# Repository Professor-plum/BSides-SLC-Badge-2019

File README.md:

# BSides-SLC-Badge-2019
source code, design files and artwork used in the BSides SLC 2019 badge

The following libraries were utilized in this project

https://github.com/rogerclarkmelbourne/Arduino_STM32
https://github.com/PaulStoffregen/SerialFlash
https://github.com/PaulStoffregen/XPT2046_Touchscreen

After installing these libraries, one edit needs to be made:

```
vim ~/Documents/Arduino/libraries/SerialFlash/SerialFlashChip.cpp
```

On line 161, change `SPIPORT.transfer(p, rdlen);` to be `SPIPORT.read(p, rdlen);`. I'm not sure if this is a bug in SerialFlash, or if SerialFlash was just designed to use a different STM32 library.

Now, in the Arduino IDE, you can open `src/BsidesSLCBig/BsidesSLCBig.ino`. Compile using the following board settings:

```
Board: "Generic STM32F103C Series"
Variant: "STM32F103CB (20k RAM, 128k Flash)"
```

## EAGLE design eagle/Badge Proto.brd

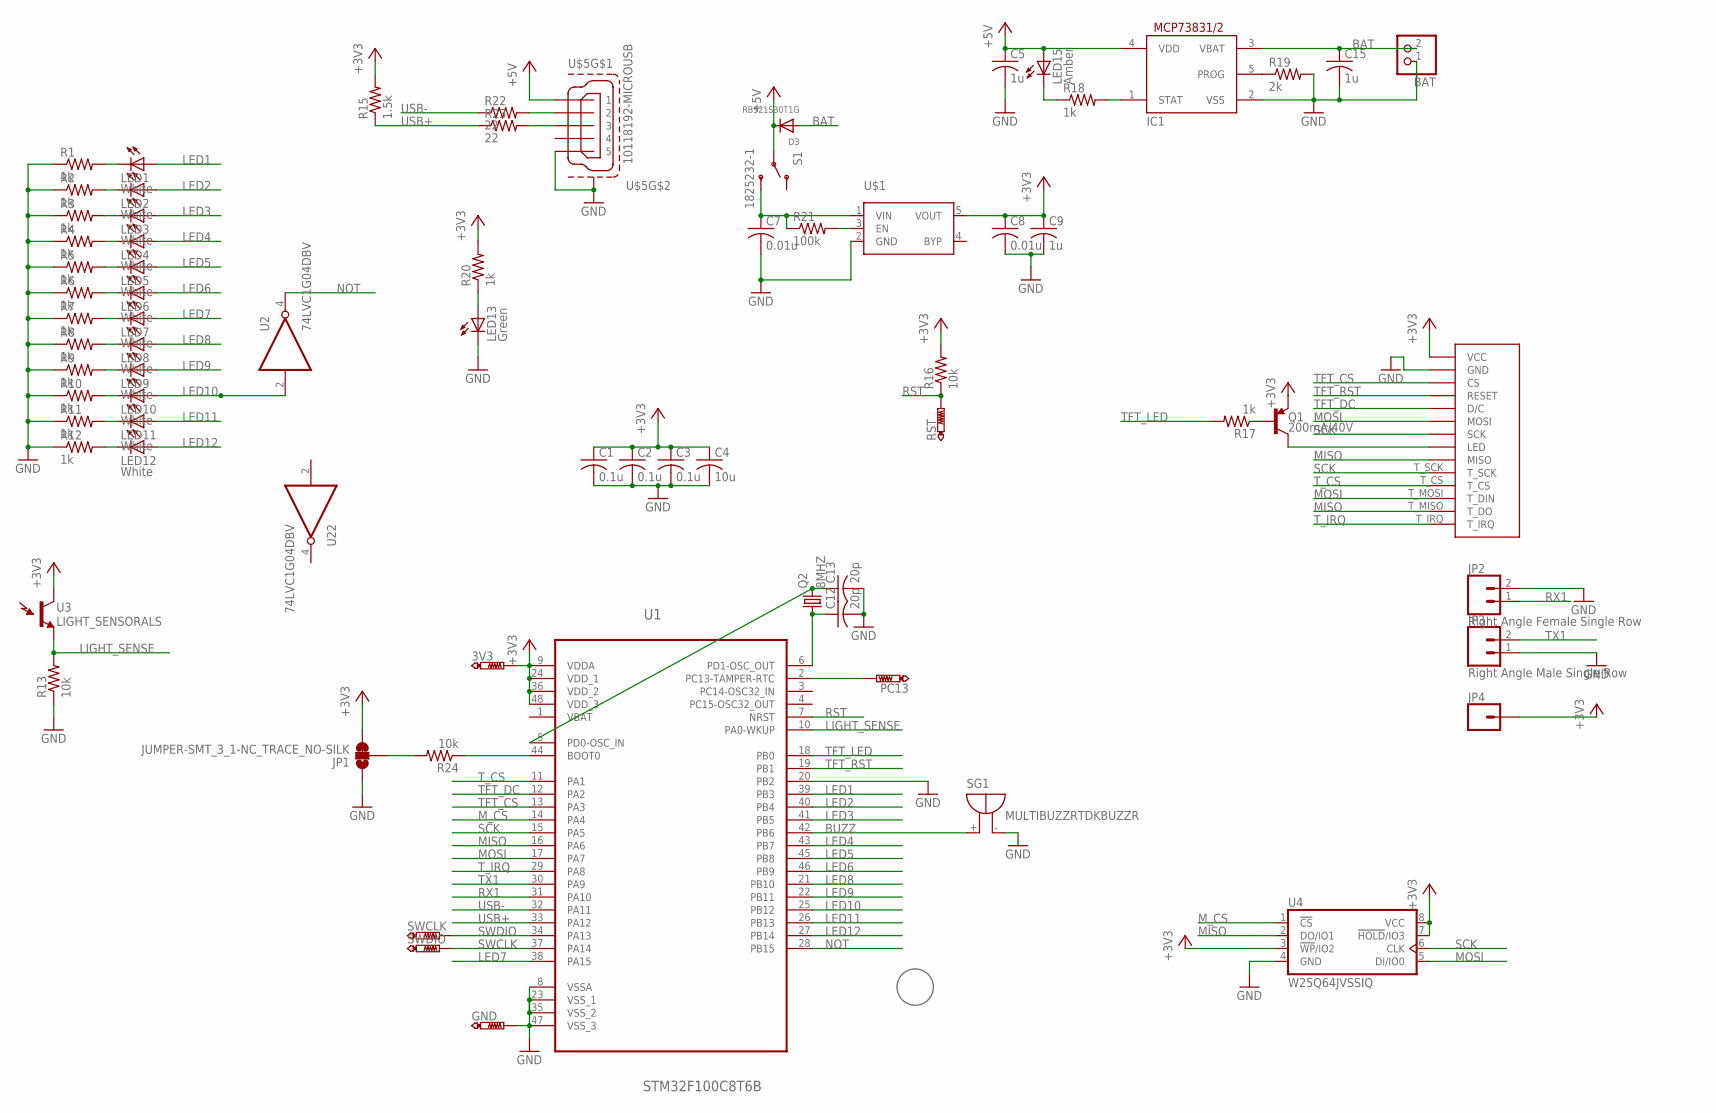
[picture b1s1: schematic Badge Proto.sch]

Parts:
3V3: PTR1TP15R; TP15R
BAT: JST_2PIN-THM-RA; JST-PH-2-THM-RA
C1, C2, C3: 0.1u; C0603K; MPN MC0603B104K160CT
C4: 10u; C0603K; MPN C1608X5R1A106K080AC
C5, C9, C15: 1u; C0603K; MPN C0603C104K8RACTU
C7, C8: 0.01u; C0603K
C12, C13: 20p; C0603K
D3: RB521S30T1G; SOD-523; MPN 1N4148WT.
GND: PTR1TP15R; TP15R
IC1: MCP73831/OT; SOT23-5L
J1: SPI_TFT_DISPLAY_TOUCH_NOSD; SPI_DISPLAY_TOUCH_NOSD
JP1: JUMPER-SMT_3_1-NC_TRACE_NO-SILK; SMT-JUMPER_3_1-NC_TRACE_NO-SILK
JP2: Right Angle Female Single Row; 1X02_RA_PTH_FEMALE
JP3: Right Angle Male Single Row; 1X02_RA_PTH_FEMALE
JP4: CONN_01PTH_NO_SILK_YES_STOP; 1X01_NO_SILK
LED1, LED2, LED3, LED4, LED5, LED6, LED7, LED8, LED9, LED10, LED11, LED12: White; SML0603
LED13: Green; SML0603
LED15: Amber; SML0603; MPN ASMT-RJ45-AQ502
PC13: PTR1TP15R; TP15R
Q1: 200mA/40V; SOT23-3
Q2: 8MHZ; HC49/S
R1, R2, R3, R4, R5, R6, R7, R8, R9, R10, R11, R12, R17, R18, R20: 1k; R0603; MPN ERJ-3GEYJ912V
R13, R16, R24: 10k; R0603; MPN RR0816P-103-D
R15: 1.5k; R0603; MPN MC0603SAF1501T5E
R19: 2k; R0603; MPN ERJ-6ENF2001V
R21: 100k; R0603; MPN MC0603SAF1003T5E
R22, R23: 22; R0603; MPN ERJ-3GEYJ220V
RST: PTR1TP15R; TP15R
S1: 1825232-1
SG1: MULTIBUZZRTDKBUZZR; BUZZRTDK
SWCLK: PTR1TP15R; TP15R
SWDIO: PTR1TP15R; TP15R
U1: STM32F100C8T6B; QFP50P900X900X160-48N
U2, U22: 74LVC1G04DBV; SOT23-5; MPN SN74LVC1G04DBVR
U3: LIGHT_SENSORALS; ALS-PT19
U4: W25Q64JVSSIQ; SO08-SS
U$1: SPX3819; SOT23-5
U$4: PLUM
U$5: 10118192-MICROUSB; MICROUSB-SMT; MPN 10118192-0002LF

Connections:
+3V3: 3V3.TP, C1.1, C2.1, C3.1, C4.1, C8.1, C9.1, J1.VCC, JP4.1, Q1.2 (E), R15.2, R16.2, R20.2, U1.9 (VDDA), U1.24 (VDD_1), U1.36 (VDD_2), U1.48 (VDD_3), U2.5 (VCC), U3.C (C1), U4.3 (!WP!/IO2), U4.7 (!HOLD!/IO3), U4.8 (VCC), U22.5 (VCC), U$1.5 (VOUT)
+5V: C5.1, D3.K (C), IC1.4 (VDD), LED15.A, S1.2, U$5.P$1 (1)
BAT: BAT.2, C15.1, D3.A, IC1.3 (VBAT)
BUZZ: SG1.+, U1.42 (PB6)
GND: BAT.1, C1.2, C2.2, C3.2, C4.2, C5.2, C7.2, C8.2, C9.2, C12.2, C13.2, C15.2, GND.TP, IC1.2 (VSS), J1.GND, JP1.1, JP2.2, JP3.1, LED13.C, R1.1, R2.1, R3.1, R4.1, R5.1, R6.1, R7.1, R8.1, R9.1, R10.1, R11.1, R12.1, R13.1, R19.2, SG1.-, U1.8 (VSSA), U1.20 (PB2), U1.23 (VSS_1), U1.35 (VSS_2), U1.47 (VSS_3), U2.3 (GND), U4.4 (GND), U22.3 (GND), U$1.2 (GND), U$5.P$5 (5), U$5.SHLD@0 (S4), U$5.SHLD@1 (S4), U$5.SHLD@2 (S4), U$5.SHLD@3 (S4), U$5.SHLD@4 (S4), U$5.SHLD@5 (S4)
LED1: LED1.A, U1.39 (PB3)
LED2: LED2.A, U1.40 (PB4)
LED3: LED3.A, U1.41 (PB5)
LED4: LED4.A, U1.43 (PB7)
LED5: LED5.A, U1.45 (PB8)
LED6: LED6.A, U1.46 (PB9)
LED7: LED7.A, U1.38 (PA15)
LED8: LED8.A, U1.21 (PB10)
LED9: LED9.A, U1.22 (PB11)
LED10: LED10.A, U1.25 (PB12), U2.2 (I)
LED11: LED11.A, U1.26 (PB13)
LED12: LED12.A, U1.27 (PB14)
LIGHT_SENSE: R13.2, U1.10 (PA0-WKUP), U3.E (E1)
MISO: J1.MISO, J1.T_MISO (T_DO), U1.16 (PA6), U4.2 (DO/IO1)
MOSI: J1.MOSI, J1.T_MOSI (T_DIN), U1.17 (PA7), U4.5 (DI/IO0)
M_CS: U1.14 (PA4), U4.1 (!CS!)
unnamed: LED1.C, R1.2
unnamed: LED2.C, R2.2
unnamed: LED3.C, R3.2
unnamed: LED4.C, R4.2
unnamed: LED5.C, R5.2
unnamed: LED6.C, R6.2
unnamed: LED7.C, R7.2
unnamed: LED8.C, R8.2
unnamed: LED9.C, R9.2
unnamed: R22.2, U$5.P$2 (2)
unnamed: R23.2, U$5.P$3 (3)
unnamed: R21.2, U$1.3 (EN)
unnamed: Q1.1 (B), R17.1
unnamed: IC1.5 (PROG), R19.1
unnamed: JP1.2, R24.2
unnamed: C12.1, Q2.1, U1.6 (PD1-OSC_OUT)
unnamed: C13.1, Q2.2, U1.5 (PD0-OSC_IN)
unnamed: LED15.C, R18.1
unnamed: IC1.1 (STAT), R18.2
unnamed: LED10.C, R10.2
unnamed: LED11.C, R11.2
unnamed: LED12.C, R12.2
unnamed: LED13.A, R20.1
unnamed: C7.1, R21.1, S1.1, U$1.1 (VIN)
unnamed: R24.1, U1.44 (BOOT0)
unnamed: PC13.TP, U1.2 (PC13-TAMPER-RTC)
NOT: U1.28 (PB15), U2.4 (O)
NS1: J1.LED, Q1.3 (C)
RST: R16.1, RST.TP, U1.7 (NRST)
RX1: JP2.1, U1.31 (PA10)
SCK: J1.SCK, J1.T_SCK, U1.15 (PA5), U4.6 (CLK)
SWCLK: SWDIO.TP, U1.37 (PA14)
SWDIO: SWCLK.TP, U1.34 (PA13)
TFT_CS: J1.CS, U1.13 (PA3)
TFT_DC: J1.D/C, U1.12 (PA2)
TFT_LED: R17.2, U1.18 (PB0)
TFT_RST: J1.RESET, U1.19 (PB1)
TX1: JP3.2, U1.30 (PA9)
T_CS: J1.T_CS, U1.11 (PA1)
T_IRQ: J1.T_IRQ, U1.29 (PA8)
USB+: R15.1, R23.1, U1.33 (PA12)
USB-: R22.1, U1.32 (PA11)
VBAT: U1.1 (VBAT)

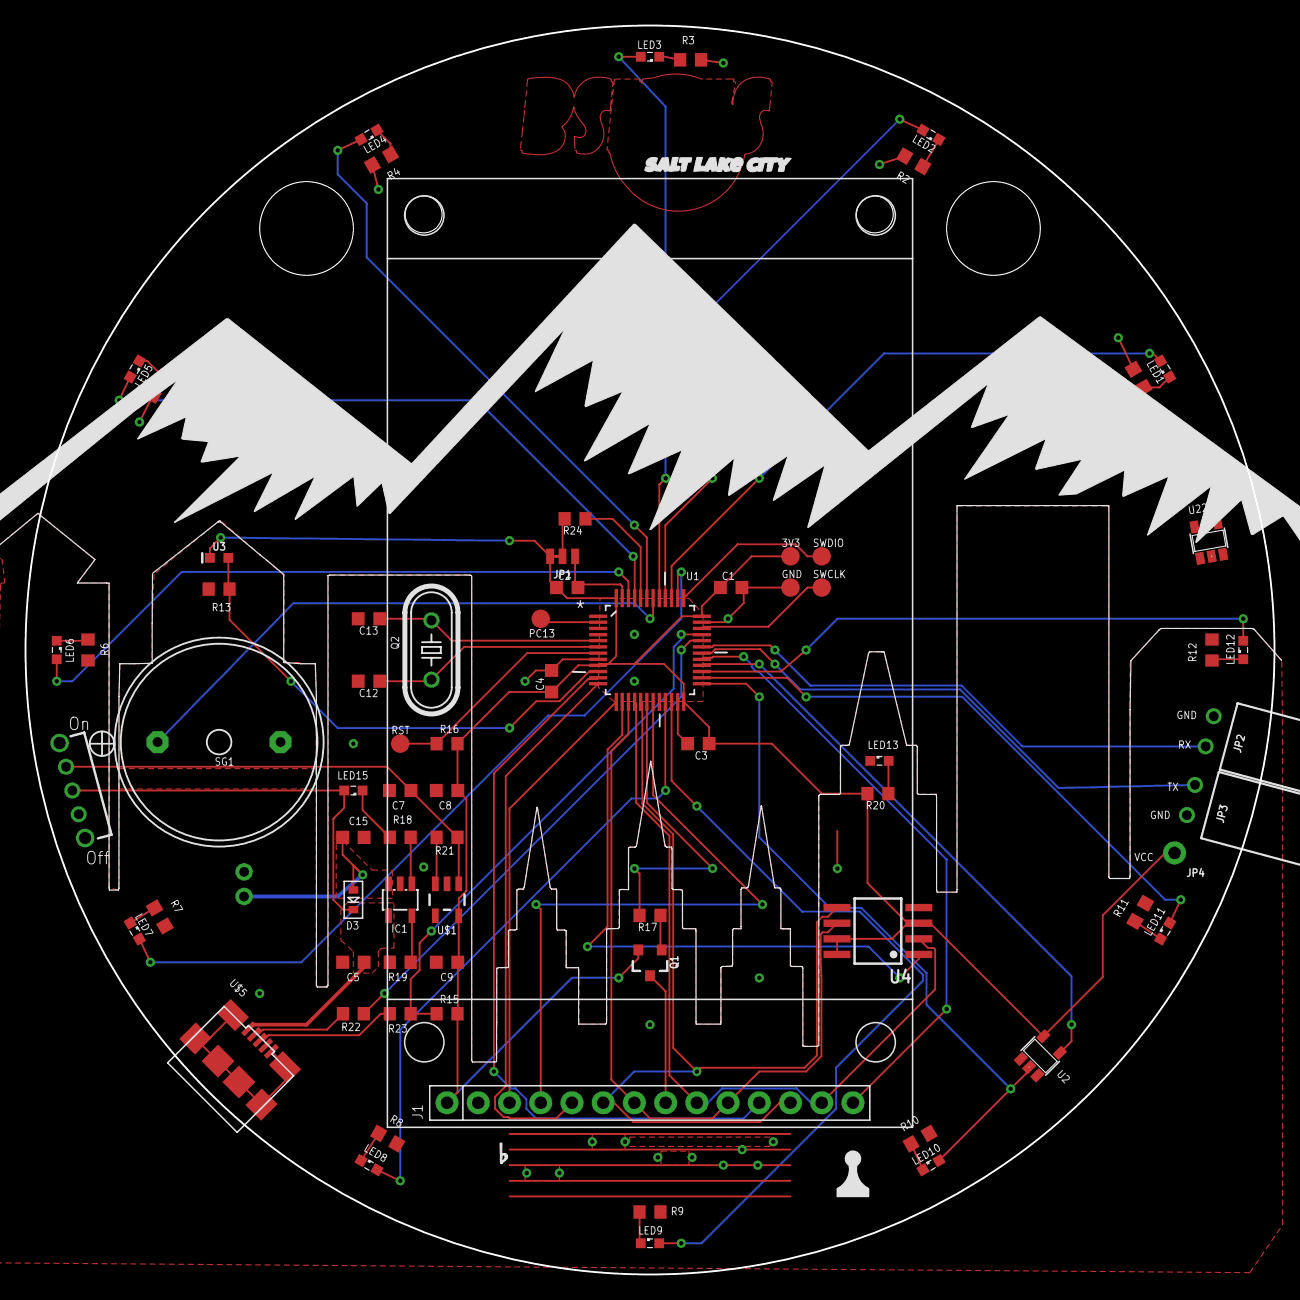
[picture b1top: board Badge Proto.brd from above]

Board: 2 copper layers, 101.6 x 101.6 mm, 74 parts (1 on the bottom side), 63 nets.

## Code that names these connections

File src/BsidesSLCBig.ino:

#include <SPI.h>
#include <Adafruit_ILI9341_STM.h>
#include <XPT2046_Touchscreen.h>
#include <LedWheel.h>
#include <EEPROM.h>

#include "Room.h"
#include "FlashReader.h"

#include "AlleyRoom.h"
#include "DialRoom.h"
#include "MarketRoom.h"
#include "GameRoom.h"
#include "MainFrameRoom.h"
#include "TVRoom.h"
#include "StreetRoom.h"
#include "ArcadeRoom.h"
#include "TowerRoom.h"
#include "KeypadRoom.h"
#include "PuzzleRoom.h"
#include "NightClub.h"
#include "DJRoom.h"
#include "PanelRoom.h"
#include "SplashRoom.h"
#include "EndRoom.h"


#define TFT_DC    PA2
#define TFT_RST   PB1 
#define TFT_CS    PA3
#define TFT_LED   PB0

#define SF_CS     PA4

#define T_CS      PA1
#define T_IRQ     PA8

#define BUZZ      PB6 

#define MAX_LIGHT 60000

Adafruit_ILI9341_STM tft = Adafruit_ILI9341_STM(TFT_CS, TFT_DC, TFT_RST);
XPT2046_Touchscreen ts(T_CS, T_IRQ);

uint16_t TS_MINX    = 200;
uint16_t TS_MINY    = 150;
uint16_t TS_MAXX    = 3800;
uint16_t TS_MAXY    = 3700;

Room *cur;

void calibrate();
bool ask();

const char* peermsg[] = {
  "1-AGILE",
  "2-DRIVE",
  "3-MIGHT",
  "4-HEART",
  "5-VIGOR"
};

void setup() {
  Serial.begin(19200);
  
  pinMode(PA10, INPUT_PULLUP);
  //Serial1.begin(9600);
  
  FR.begin(SF_CS);
  
  tft.begin();
  //tft.setRotation(1);
  tft.fillScreen(ILI9341_BLUE);
  
  ts.begin();
  ts.setRotation(3);



  pinMode(LIGHT, INPUT_ANALOG);
  randomSeed(analogRead(LIGHT)); 
  
  EEPROM.init();
  
  peer_id = EEPROM.read(10);
  if ((peer_id <=0) || (peer_id > 5)) {
    peer_id = (rand() % 5) +1;
    //Serial.print("Invalid peer_id, Resetting to ");Serial.println(peer_id);
    EEPROM.write(10, peer_id);
    EEPROM.write(50, TS_MINX);
    EEPROM.write(52, TS_MINY);
    EEPROM.write(54, TS_MAXX);
    EEPROM.write(56, TS_MAXY);
  }
  else {
    TS_MINX = EEPROM.read(50);
    TS_MINY = EEPROM.read(52);
    TS_MAXX = EEPROM.read(54);
    TS_MAXY = EEPROM.read(56);
  }
  for (int i=0; i< 5; i++) {
    if (EEPROM.read(40+i) == 0xcc)
      peers[i] = true;
  }




  for (int i=0; i<12; ++i)
    pinMode(ledMap[i], OUTPUT);

  for (int i=11; i>=0; --i) {
    digitalWrite(ledMap[i], HIGH);
    delay(50);
    digitalWrite(ledMap[i], LOW);
  }

  wheel_init();
  wavInit();

  pinMode(NOTPIN, INPUT);

  cur =  new SplashRoom(); 
  cur->refresh(&tft, 0);

}

uint32_t last=0;
uint32_t lastDraw=0;
int backlight = MAX_LIGHT;
bool touched = false;
bool sleeping = false;
TS_Point p;
uint32_t lastSerial = 0;

void loop() {
  uint32_t now=millis();
  uint32_t dt = now - last;
  last = now;

  if (sleeping) {
      if (ts.touched()) {
        SerialFlash.wakeup();
        SPI.beginTransaction(SPISettings(48000000, MSBFIRST, SPI_MODE0, DATA_SIZE_16BIT));
        tft.exitSleepMode();
        sleeping = false;
      }
      return; //early out
    }

  wavCheckBuff();

  if (true){//(now - lastDraw > 100) { //shoot for 10 fps, may not achieve this
    SPI.beginTransaction(SPISettings(48000000, MSBFIRST, SPI_MODE0, DATA_SIZE_16BIT));
    roomID id = cur->update(&tft, now);
    lastDraw = now;
    if (id == R_CONFIGURE) {
      calibrate();
      if (ask("Do you want to reset progress?")) {
        for (int i=0; i<12; ++i)
          EEPROM.update(20+i, 0);
        EEPROM.update(10, 0xff);
        for (int i=0; i<6; ++i)
          EEPROM.update(40+i, 0);
      }
      /*if (ask("Do you want to reprogram the flash?"))
        if (ask("Are you sure, this will wipe all data?!"))
          WriteFlash(&tft);*/
      nvic_sys_reset();
    }
    else if (id != R_NOCHANGE) {
      delete cur;
      switch(id) {
        case R_ALLEY:
          cur = new AlleyRoom();
          break;
        case R_TV:
          cur = new TVRoom();
          break;
        case R_MARKET:
          cur = new MarketRoom();
          break;
        case R_DIAL:
          cur = new DialRoom();
          break;
        case R_MAINFRAME:
          cur = new MainFrameRoom();
          break;
        case R_STREET:
          cur= new StreetRoom();
          break;
        case R_NIGHTCLUB:
          cur= new NightClub();
          break;
        case R_ARCADE:
          cur = new ArcadeRoom();
          break;
        case R_GAME:
          cur = new GameRoom();
          break;
        case R_DJ:
          cur = new DJRoom(); 
          break;
        case R_PUZZLE:
          cur= new PuzzleRoom();
          break;
        case R_KEYPAD:
          cur = new KeypadRoom();
          break;
        case R_TOWER:
          cur = new TowerRoom();
          break;
        case R_PANEL:
          cur = new PanelRoom();
          break;
        case R_SPLASH:
          cur = new SplashRoom();
          break;
        case R_END:
          cur = new EndRoom();
          break;
      }
      SPI.beginTransaction(SPISettings(48000000, MSBFIRST, SPI_MODE0, DATA_SIZE_16BIT));
      tft.fillScreen(ILI9341_BLACK);
      cur->refresh(&tft, now);
    }
  }

  wavCheckBuff();
    
  if (ts.touched()) {
    p = ts.getPoint();
    backlight = MAX_LIGHT;
    digitalWrite(TFT_LED, LOW);
    int t = p.x;
    p.x = p.y;
    p.y = t;
    p.x = map(p.x, TS_MINX, TS_MAXX, 0, 240);
    p.y = map(p.y, TS_MINY, TS_MAXY, 0, 320); 
    if (touched)
      cur->touchMove(p.x, p.y);
    else {
      touched = true;
      cur->touchDown(p.x, p.y);
    }

  }
  else if (touched) {
    touched = false;
    cur->touchUp(p.x, p.y);
  }

  if (lastSerial + 2000 < now) {
    Serial.println(peermsg[peer_id-1]);
    lastSerial = now;
  }
  while (Serial.available() >= 7) {
    char rin[8] = {0};
    rin[0] = Serial.read();
    if ((rin[0] >'0') && (rin[0] < '6')) {
      for (int i=1; i<7; ++i) {
        rin[i] = Serial.read();
      }
      for (int i=0; i<5; ++i) {
        if (memcmp(rin, peermsg[i], 7)==0) {
          wavPlay("pair.wav");
          if (!peers[i]) {
            peers[i] = true;
            EEPROM.update(40+i, 0xcc);
          }
        }
      }
    }
  }

  if (backlight > 0) {
    analogWrite(TFT_LED, max(0, 255-(backlight/5)));
    backlight-=dt;
  }
  else { //Time to sleep
    SerialFlash.sleep();
    SPI.beginTransaction(SPISettings(48000000, MSBFIRST, SPI_MODE0, DATA_SIZE_16BIT));
    tft.enterSleepMode();
    sleeping = true;
    digitalWrite(TFT_LED, HIGH);
  }

}

void calibrate() {
  int poses[2] = {0,0};
  digitalWrite(TFT_LED, HIGH);
  SPI.beginTransaction(SPISettings(48000000, MSBFIRST, SPI_MODE0, DATA_SIZE_16BIT));
  tft.fillScreen(ILI9341_RED);
  tft.setTextSize(1);
  tft.setTextColor(ILI9341_BLACK);
  tft.setCursor(85, 120);
  tft.print("With pen,");
  tft.setCursor(50, 130);
  tft.print("touch top left");
  tft.setCursor(40, 140);
  tft.print("corner of screen");
  tft.drawFastHLine(1, 0, 5, ILI9341_BLACK);
  tft.drawFastVLine(0, 1, 5, ILI9341_BLACK);
  delay(500);

  for (int i=0; i< 10; ++i) {
    while (!ts.touched()) delay(50);
    TS_Point p = ts.getPoint();

    poses[1] += p.x;
    poses[0] += p.y;
  }
  TS_MINX = poses[0]/10;
  TS_MINY = poses[1]/10;
  poses[0] = poses[1] = 0;

  while (ts.touched()) delay(50);

  SPI.beginTransaction(SPISettings(48000000, MSBFIRST, SPI_MODE0, DATA_SIZE_16BIT));
  tft.fillScreen(ILI9341_GREEN);
  tft.setCursor(85, 120);
  tft.print("With pen,");
  tft.setCursor(20, 130);
  tft.print("touch bottom right");
  tft.setCursor(40, 140);
  tft.print("corner of screen");
  tft.drawFastHLine(234, 319, 5, ILI9341_BLACK);
  tft.drawFastVLine(239, 314, 5, ILI9341_BLACK);  
  delay(1000);

  for (int i=0; i< 10; ++i) {
    while (!ts.touched()) delay(50);
    TS_Point p = ts.getPoint();

    poses[1] += p.x;
    poses[0] += p.y;
  }
  TS_MAXX = poses[0]/10;
  TS_MAXY = poses[1]/10; 

  EEPROM.update(50, TS_MINX);
  EEPROM.update(52, TS_MINY);
  EEPROM.update(54, TS_MAXX);
  EEPROM.update(56, TS_MAXY);

  /*Serial.println(TS_MINX);
  Serial.println(TS_MINY);
  Serial.println(TS_MAXX);
  Serial.println(TS_MAXY);*/

  SPI.beginTransaction(SPISettings(48000000, MSBFIRST, SPI_MODE0, DATA_SIZE_16BIT));
  tft.setTextSize(1);
}

bool ask(const char* msg) {
  SPI.beginTransaction(SPISettings(48000000, MSBFIRST, SPI_MODE0, DATA_SIZE_16BIT));
  tft.fillRoundRect(2,100, 236, 100, 5, ILI9341_BLUE);
  tft.setTextColor(ILI9341_WHITE);
  tft.setCursor(10, 120);
  tft.setTextSize(1);
  tft.print(msg);
  tft.fillRoundRect(30, 170, 60, 20, 3, ILI9341_NAVY);
  tft.fillRoundRect(150, 170, 60, 20, 3, ILI9341_NAVY);
  tft.setCursor(50, 175);
  tft.print("Yes");
  tft.setCursor(170, 175);
  tft.print("No");
  delay(500);

  while (true) {
    if (ts.touched()) {
      TS_Point p = ts.getPoint();
      int t = p.x;
      p.x = p.y;
      p.y = t;
      p.x = map(p.x, TS_MINX, TS_MAXX, 0, 240);
      p.y = map(p.y, TS_MINY, TS_MAXY, 0, 320); 
      if ((p.y > 170) && (p.y < 190)){
        if ((p.x>30) && (p.x<90)) return true;
        if ((p.x>150) && (p.x<210)) return false;
      }
    }
    delay(50);
  }
  SPI.beginTransaction(SPISettings(48000000, MSBFIRST, SPI_MODE0, DATA_SIZE_16BIT));
}

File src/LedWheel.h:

#ifndef LEDWHEEL
#define LEDWHEEL
#include <Arduino.h>

#define ledTimer	Timer2
const char ledMap[12] = {PB3, PB4, PB5, PB7, PB8, PB9, PA15, PB10, PB11, PB12, PB13, PB14};

void wheel_init();
void wheel_set(int id, bool on);
bool wheel_get(int id);
bool wheel_complete();

#endif

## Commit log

2019-02-22 Added code and images
2019-02-23 Added slides
2019-02-25 Added missing images
2019-03-01 folder structure for Arduino IDE
2019-03-01 Changes needed to get it to compile: Added NES.h 'Sleep' extension for STM lib Updated a handful of #include statements to use local source files instead of libraries
2019-03-01 updated build instructions

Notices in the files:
parts and their libraries:
SparkFun-Sensors: Licensing: Creative Commons ShareAlike 4.0 International - https://creativecommons.org/licenses/by-sa/4.0
memory-winbond: Copyright (C) 2010, Bob Starr
